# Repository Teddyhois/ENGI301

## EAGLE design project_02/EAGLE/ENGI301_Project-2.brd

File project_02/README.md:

# Guest Counter PCB

The Guest Counter is a device that uses two IR distance sensors to sense people walking into a room. When a person is detected, a short jingle plays through a speaker and the total number of people in the room, people who entered the room, and people who exited the room are updated and displayed on an OLED display. The user can reset the tallies by holding down the push button on the board.

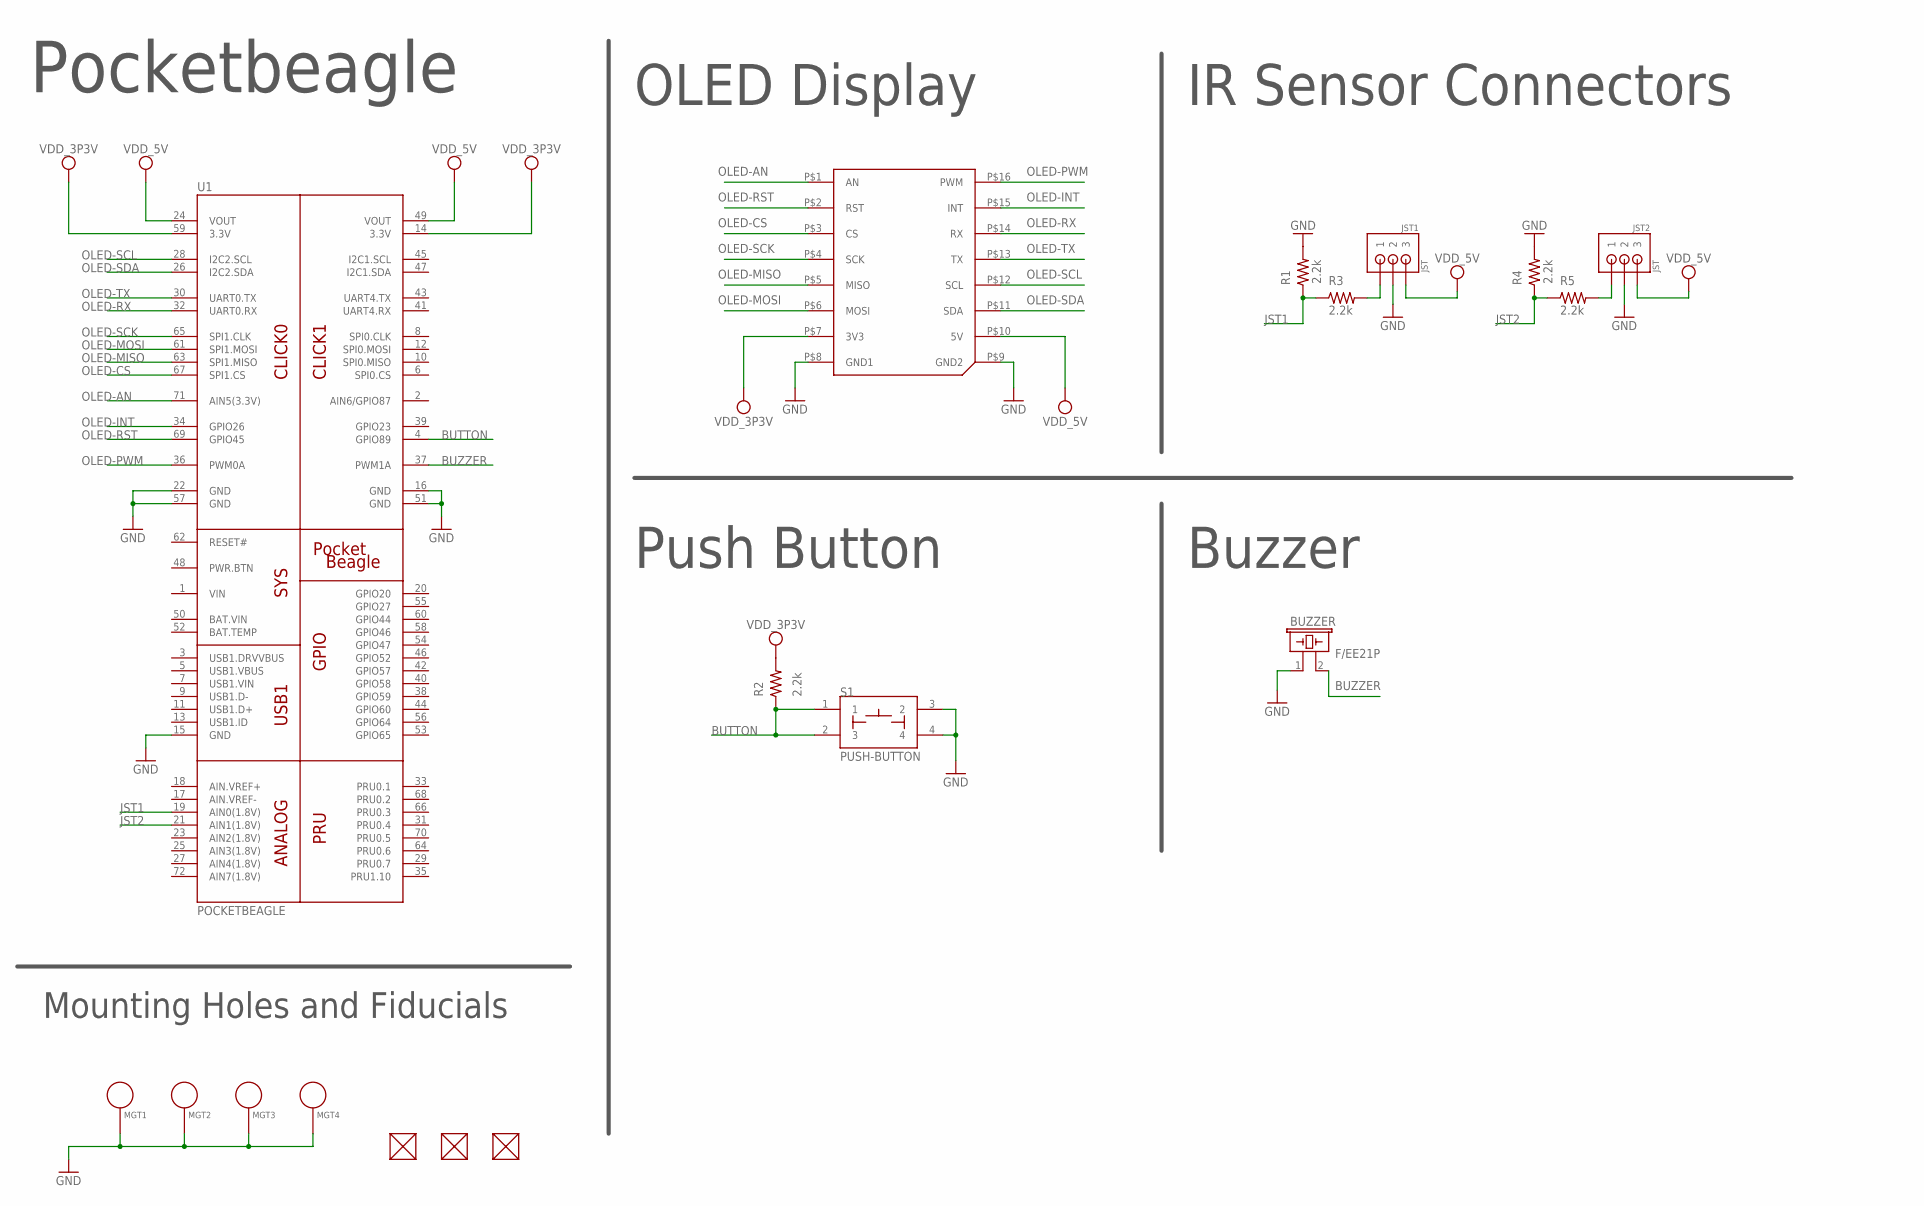
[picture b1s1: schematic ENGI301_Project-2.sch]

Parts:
BUZZER: F/EE21P
FUD1, FUD2, FUD3: FIDUCIAL; FIDUCIAL_40MIL
JST1, JST2: JST; JST_HEADER
MGT1, MGT2, MGT3, MGT4: MOUNTING_HOLE
R1, R2, R3, R4, R5: 2.2k; R0603
S1: PUSH-BUTTON; BUTTON_12.5MM
U1: POCKETBEAGLE
U2: MIKROE_CLICKLARGE; MIKROE_BUS_LARGE

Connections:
BAT.VIN: U1.50 (BAT.VIN)
BUTTON: R2.1, S1.1, S1.2 (3), U1.4 (GPIO89)
BUZZER: BUZZER.2, U1.37 (PWM1A)
GND: BUZZER.1, JST1.P2 (2), JST2.P2 (2), MGT1.P$1, MGT2.P$1, MGT3.P$1, MGT4.P$1, R1.2, R4.2, S1.3 (2), S1.4, U1.15 (GND), U1.16 (GND), U1.22 (GND), U1.51 (GND), U1.57 (GND), U2.P$8 (GND1), U2.P$9 (GND2)
JST1: R1.1, R3.1, U1.19 (AIN0(1.8V))
JST2: R4.1, R5.1, U1.21 (AIN1(1.8V))
unnamed: JST1.P3 (1), R3.2
unnamed: JST2.P3 (1), R5.2
OLED-AN: U1.71 (AIN5(3.3V)), U2.P$1 (AN)
OLED-CS: U1.67 (SPI1.CS), U2.P$3 (CS)
OLED-INT: U1.34 (GPIO26), U2.P$15 (INT)
OLED-MISO: U1.63 (SPI1.MISO), U2.P$5 (MISO)
OLED-MOSI: U1.61 (SPI1.MOSI), U2.P$6 (MOSI)
OLED-PWM: U1.36 (PWM0A), U2.P$16 (PWM)
OLED-RST: U1.69 (GPIO45), U2.P$2 (RST)
OLED-RX: U1.32 (UART0.RX), U2.P$14 (RX)
OLED-SCK: U1.65 (SPI1.CLK), U2.P$4 (SCK)
OLED-SCL: U1.28 (I2C2.SCL), U2.P$12 (SCL)
OLED-SDA: U1.26 (I2C2.SDA), U2.P$11 (SDA)
OLED-TX: U1.30 (UART0.TX), U2.P$13 (TX)
VDD_3P3V: R2.2, U1.14 (3.3V), U1.59 (3.3V), U2.P$7 (3V3)
VDD_5V: JST1.P1 (3), JST2.P1 (3), U1.24 (VOUT), U1.49 (VOUT), U2.P$10 (5V)
VIN: U1.1 (VIN)

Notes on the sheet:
Pocketbeagle
OLED Display
IR Sensor Connectors
Buzzer
Push Button
Mounting Holes and Fiducials

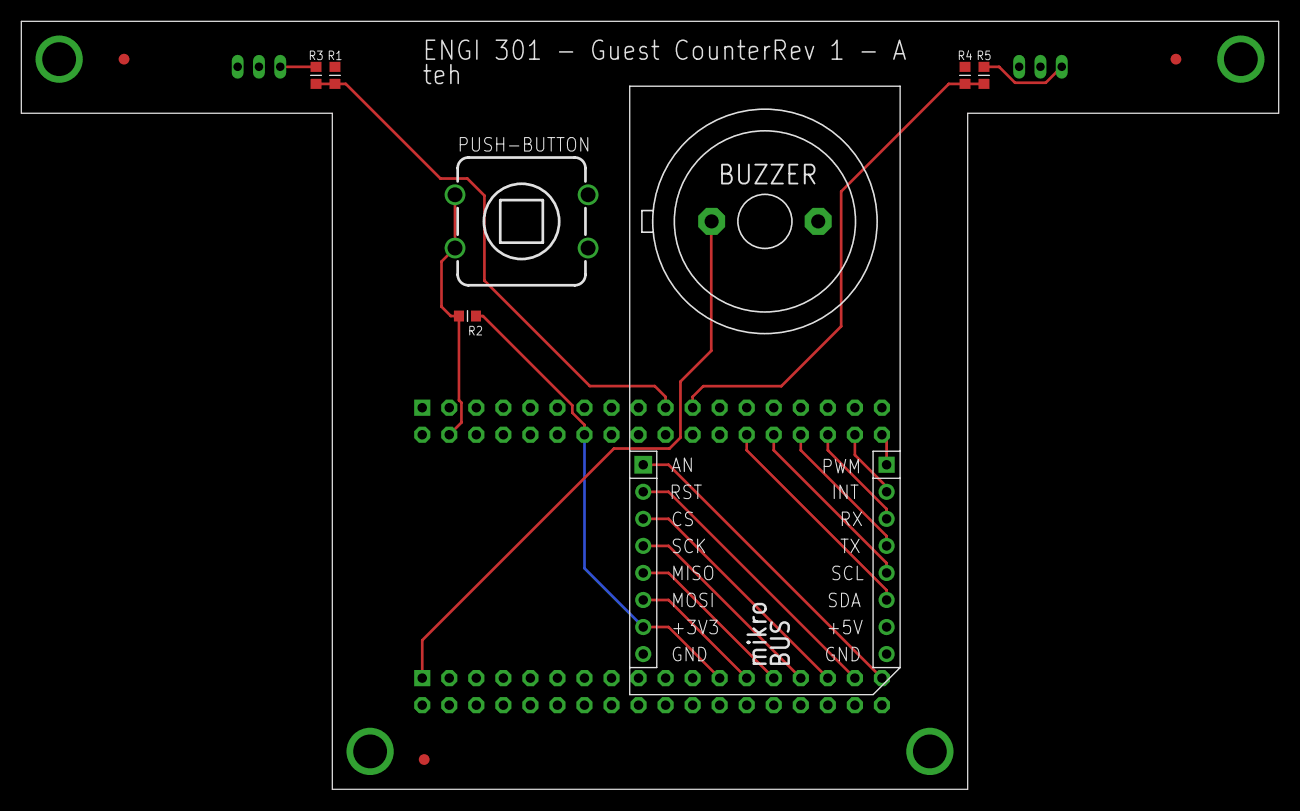
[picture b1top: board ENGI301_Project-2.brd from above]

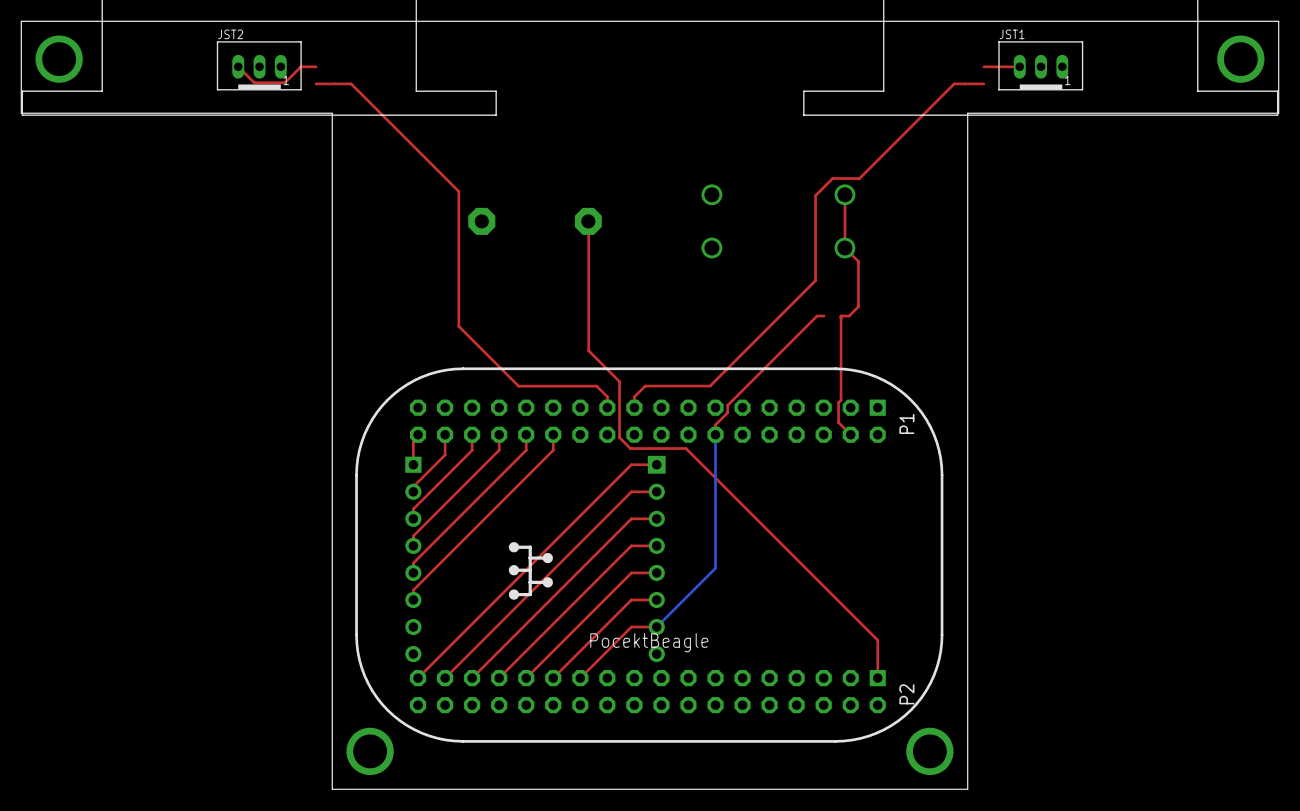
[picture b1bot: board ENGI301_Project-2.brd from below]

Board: 4 copper layers, 118.1 x 72.1 mm, 18 parts (3 on the bottom side), 21 nets.

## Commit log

2019-09-24 Repository for ENGI301 course work
2019-10-08 Assignment 5 Code
2019-10-23 Project Proposal
2019-11-11 After MUCH troubleshooting, created python code to measure distance with both ultrasonic sensors. Note: Currently having issue with sensors cutting off and not returning values.
2019-11-11 Fixed copyright
2019-11-19 Uploaded Project code
2019-11-19 Uploaded display device tree overlay
2019-11-19 Rename README.md.txt to README.md
2019-11-27 Project 2 Proposal
2019-12-17 Project_2 Upload
